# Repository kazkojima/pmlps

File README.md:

# PMLPS : Poor Man's Local Positioning System

Local positioning system using OpenMV cam M7. The blob data is sent to the host PC with UDP by ESP32 connected to cam via SPI.

This program uses libvsr Geometric Algebra library:
http://versor.mat.ucsb.edu/
Setup libvsr first. Makefile assumes that pslps and versor(libvsr) directories are in the same parent directory.

Caveat: Everything is experimental.

[OpenVM cam M7] <-- SPI --> [ESP32] <-- UDP/WiFi --> [Host PC]

SPI connection is here:

| OpenVM/M7(parent) | ESP32(child)    |
| ----------------- |:---------------:|
| P0(MOSI)          | IO23(MOSI)      |
| P1(MISO)          | IO19(MISO)      |
| P2(SCK)           | IO18(CLK)       |
| P3(NSS)           | IO5(CS)         |
| P4(HANDSHAKE)     | IO22(HANDSHAKE) |

These ESP32 IO pins are default and configurable when building esp32 firmware.

The 3 directories below are corresponding to the above 3 componets, OpenVM cam M7, ESP32 and HOst PC.

openmv/:
  led_maker_tracking.py which is a MicroPython script for openmv cam.

esp32/:
  sender application on esp-idf. Require esp-idf environment. Configure with 'make menuconfig' for your Wi-Fi setting.

host/:
  pmlps host program. Currently send VISION_POSITION_DELTA mavlink messages to tcp:192.168.11.1:5900 which is assumed to be the telemetry port of arducopter.
  Highly experimental.

There is a tiny article for this positioning system:
https://kazkojima.github.io/pmlps-en.html

##  optional daughter board

daughter-hardware/ is a optional directory for a simple ESP32 daughter board for OpenMV cam M7 instead of usual ESP32 devkit boards. See daughter-hardware/ for its KiCad files and others. It's a simple ESP-WROOM-32 board with the connector for ST's VL53L1X breakout.

If you enable VL53L1X_ENABLE during configuring ESP-WROOM-32 firmware in esp32/, you have to make a symbolic link esp32/main/symlink-STM32CubeExpansion_53L1A1_V1.0.0 to ST's driver tree. See 
https://kazkojima.github.io/esp32-vl53l1x.html
for detail.

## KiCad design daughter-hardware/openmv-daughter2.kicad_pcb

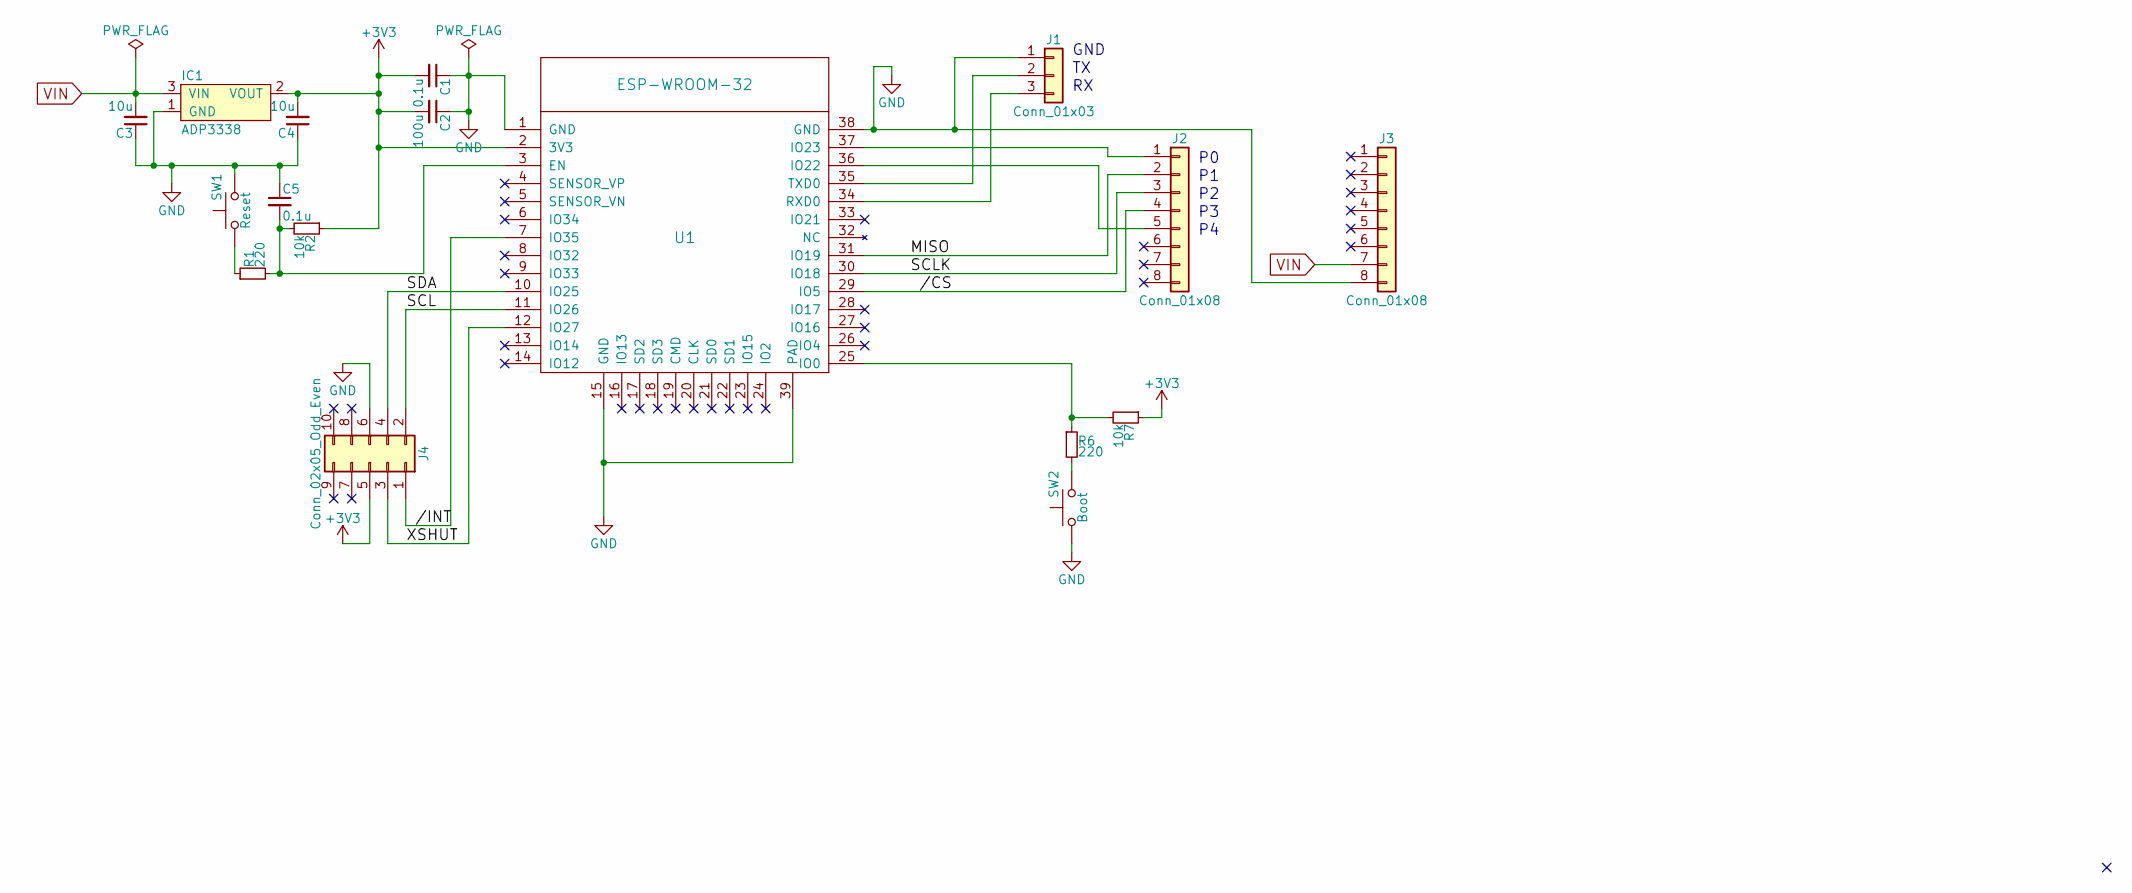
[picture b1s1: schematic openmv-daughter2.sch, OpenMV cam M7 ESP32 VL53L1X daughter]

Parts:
C1: 0.1u; C_0603_HandSoldering
C2: 100u; C_1210_HandSoldering
C3, C4: 10u; C_0603_HandSoldering
C5: 0.1u; C_0603
IC1: ADP3338; SOT-223; Farnell 1651284
J1: Conn_01x03; Pin_Header_Straight_1x03_Pitch2.54mm
J2, J3: Conn_01x08; Pin_Header_Straight_1x08_Pitch2.54mm
J4: Conn_02x05_Odd_Even; Pin_Header_Straight_Flip_2x05_Pitch2.54mm
R1, R6: 220; R_0603
R2, R7: 10k; R_0603
SW1: Reset; SW_SPST_B3U-1100P
SW2: Boot; SW_SPST_B3U-1100P
U1: ESP-WROOM-32; ESP32-WROOM-fixed

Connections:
+3V3: C1.2, C2.2, C4.2, IC1.2 (VOUT), J4.5, R2.1, R7.1, U1.2 (3V3)
//CS: J2.4, U1.29 (IO5)
//INT: J4.1, U1.7 (IO35)
/MISO: J2.2, U1.31 (IO19)
/SCL: J4.2, U1.11 (IO26)
/SCLK: J2.3, U1.30 (IO18)
/SDA: J4.4, U1.10 (IO25)
/XSHUT: J4.3, U1.12 (IO27)
GND: C1.1, C2.1, C3.1, C4.1, C5.1, IC1.1 (GND), J1.1, J3.8, J4.6, SW1.2, SW2.1, U1.1 (GND), U1.15 (GND), U1.38 (GND), U1.39 (PAD)
unnamed: C5.2, R1.2, R2.2, U1.3 (EN)
unnamed: J1.2, U1.35 (TXD0)
unnamed: J1.3, U1.34 (RXD0)
unnamed: J2.1, U1.37 (IO23)
unnamed: J2.5, U1.36 (IO22)
unnamed: R1.1, SW1.1
unnamed: R6.1, R7.2, U1.25 (IO0)
unnamed: R6.2, SW2.2
VIN: C3.2, IC1.3 (VIN), J3.7

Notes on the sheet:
GND

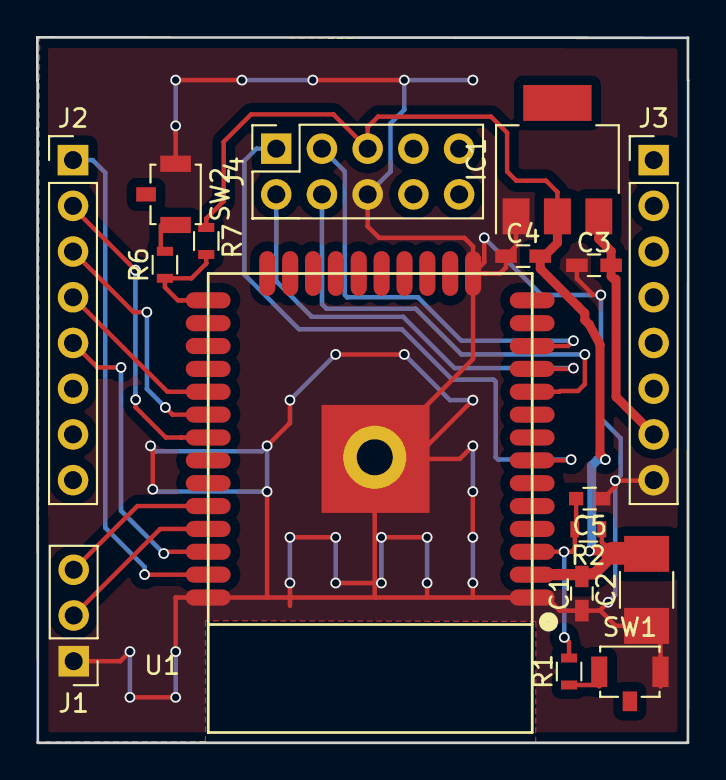
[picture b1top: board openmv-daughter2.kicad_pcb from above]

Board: 2 copper layers, 36.2 x 39.2 mm, 17 parts (0 on the bottom side), 18 nets.

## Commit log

2018-01-27 Add COPYING file
2018-02-05 Add Kalman filter for estimation of height. Add mavlink_vo.cpp.
2018-02-05 Update README.md.
2018-02-06 Add yaw.cpp and config.h.
2018-02-07 Handle ECONNRESET error.
2018-02-07 Update README.md (Take 2)
2018-02-09 Adjust 3D center position with frame ATTITUDE. Fix some thinko.
2018-02-09 Add comments. Remove #if 0'ed code.
2018-02-09 Fix comment.
2018-02-10 find_frame: Take the previous makers into account.
2018-02-10 Make visual yaw estimating more robust.
2018-02-10 Adjust visual yaw estimate filter constant. Don't send unstable VISION_POSITION_DELTA.
2018-02-10 Comment out a debug message.
2018-02-12 estimate_visual_yaw: Take pitch angle into account.
2018-02-13 estimate_visual_yaw: Use GA instead of spherical angles during adjusting with attitude.
2018-02-14 estimate_visual_yaw: Use a bit exact GA when adjusting with attitude.
2018-02-14 estimate_visual_yaw: Add a lost line.
2018-02-18 mavlink_thread: Send deltas of roll and pitch instead of angles. Fix typo.
2018-02-19 Add -d option so to specify the yaw direction offset. When no source of heading is given, ardupilot assumes null yaw. In that case, the clockwise angle from the real copter heading to the cam x-axies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
2018-02-19 Simplify lens constants. adjust_frame_center: Fix index bug. find_frame: Enable matching with the previous result.
2018-02-20 Adjust the timing of sending SET_GPS_GLOBAL_ORIGIN.
2018-02-28 Add long and long-only options. Remove unused codes.
2018-03-04 Use heading info from copter as a hint always. Add mask for persistent light points to led_maker_tracking script.
2018-03-10 Use config.cam_height instead of CAM_HEIGHT.
2018-03-13 Don't add yaw offset twice.
2018-03-26 Use a queue for estimated positions so as not to miss updates.
2018-04-04 Fix SPI pin numbers of ESP32.
2018-04-04 Oops. Fix also SPI pin function name in README.
2018-04-04 Ignore sdkconfig* so as to make esp-idf happy.
2018-04-04 Initial commit for daughter board branch.
2018-04-04 Add hardware files for the ESP32+VL53L1X daughter board on OpenMV cam.
2018-04-07 esp32: Add rcv_task which recieves packet form host. Send it to OpenMV a with possible modification.
2018-04-07 host: Send estimated position back with lens effect. openmv: Get data from esp32.
2018-04-09 Update README.
2018-04-10 Add a SPI connection picture.
2018-04-10 Add a picture to README.
2018-04-18 Add the experimental bounded ROI which is disabled by default.
2018-04-19 esp32: Add a remote switch to stop VL53L1X.
2018-04-19 host: Do range mesuements at start only.
2018-05-14 openmv/led_maker_tracking.py: Insert skipframe after disabling auto_gain and whiteblance instead before them.
2018-06-03 host: Add I3 marker support. openmv: Add led_maker_tracking_grayscale.py.
2018-06-05 host: Simplify the logic to detect I3 frame.
2018-06-05 openmv: Fix typo.
2018-07-02 host: Validate visual adjustments.
2018-10-29 host: Make --vicon-position-estimate default and add --vison-position-delta option. Adjust Kalman dynamics to more usual one.
2018-11-27 host: Include acceleration to the dynamics for Kalman filter. Add prefilter configuration.
2018-12-01 host: Add missing changes of the last commit.
2018-12-08 host: Add a non-default constructor for VisualYawEstimater. Adjust filters.
